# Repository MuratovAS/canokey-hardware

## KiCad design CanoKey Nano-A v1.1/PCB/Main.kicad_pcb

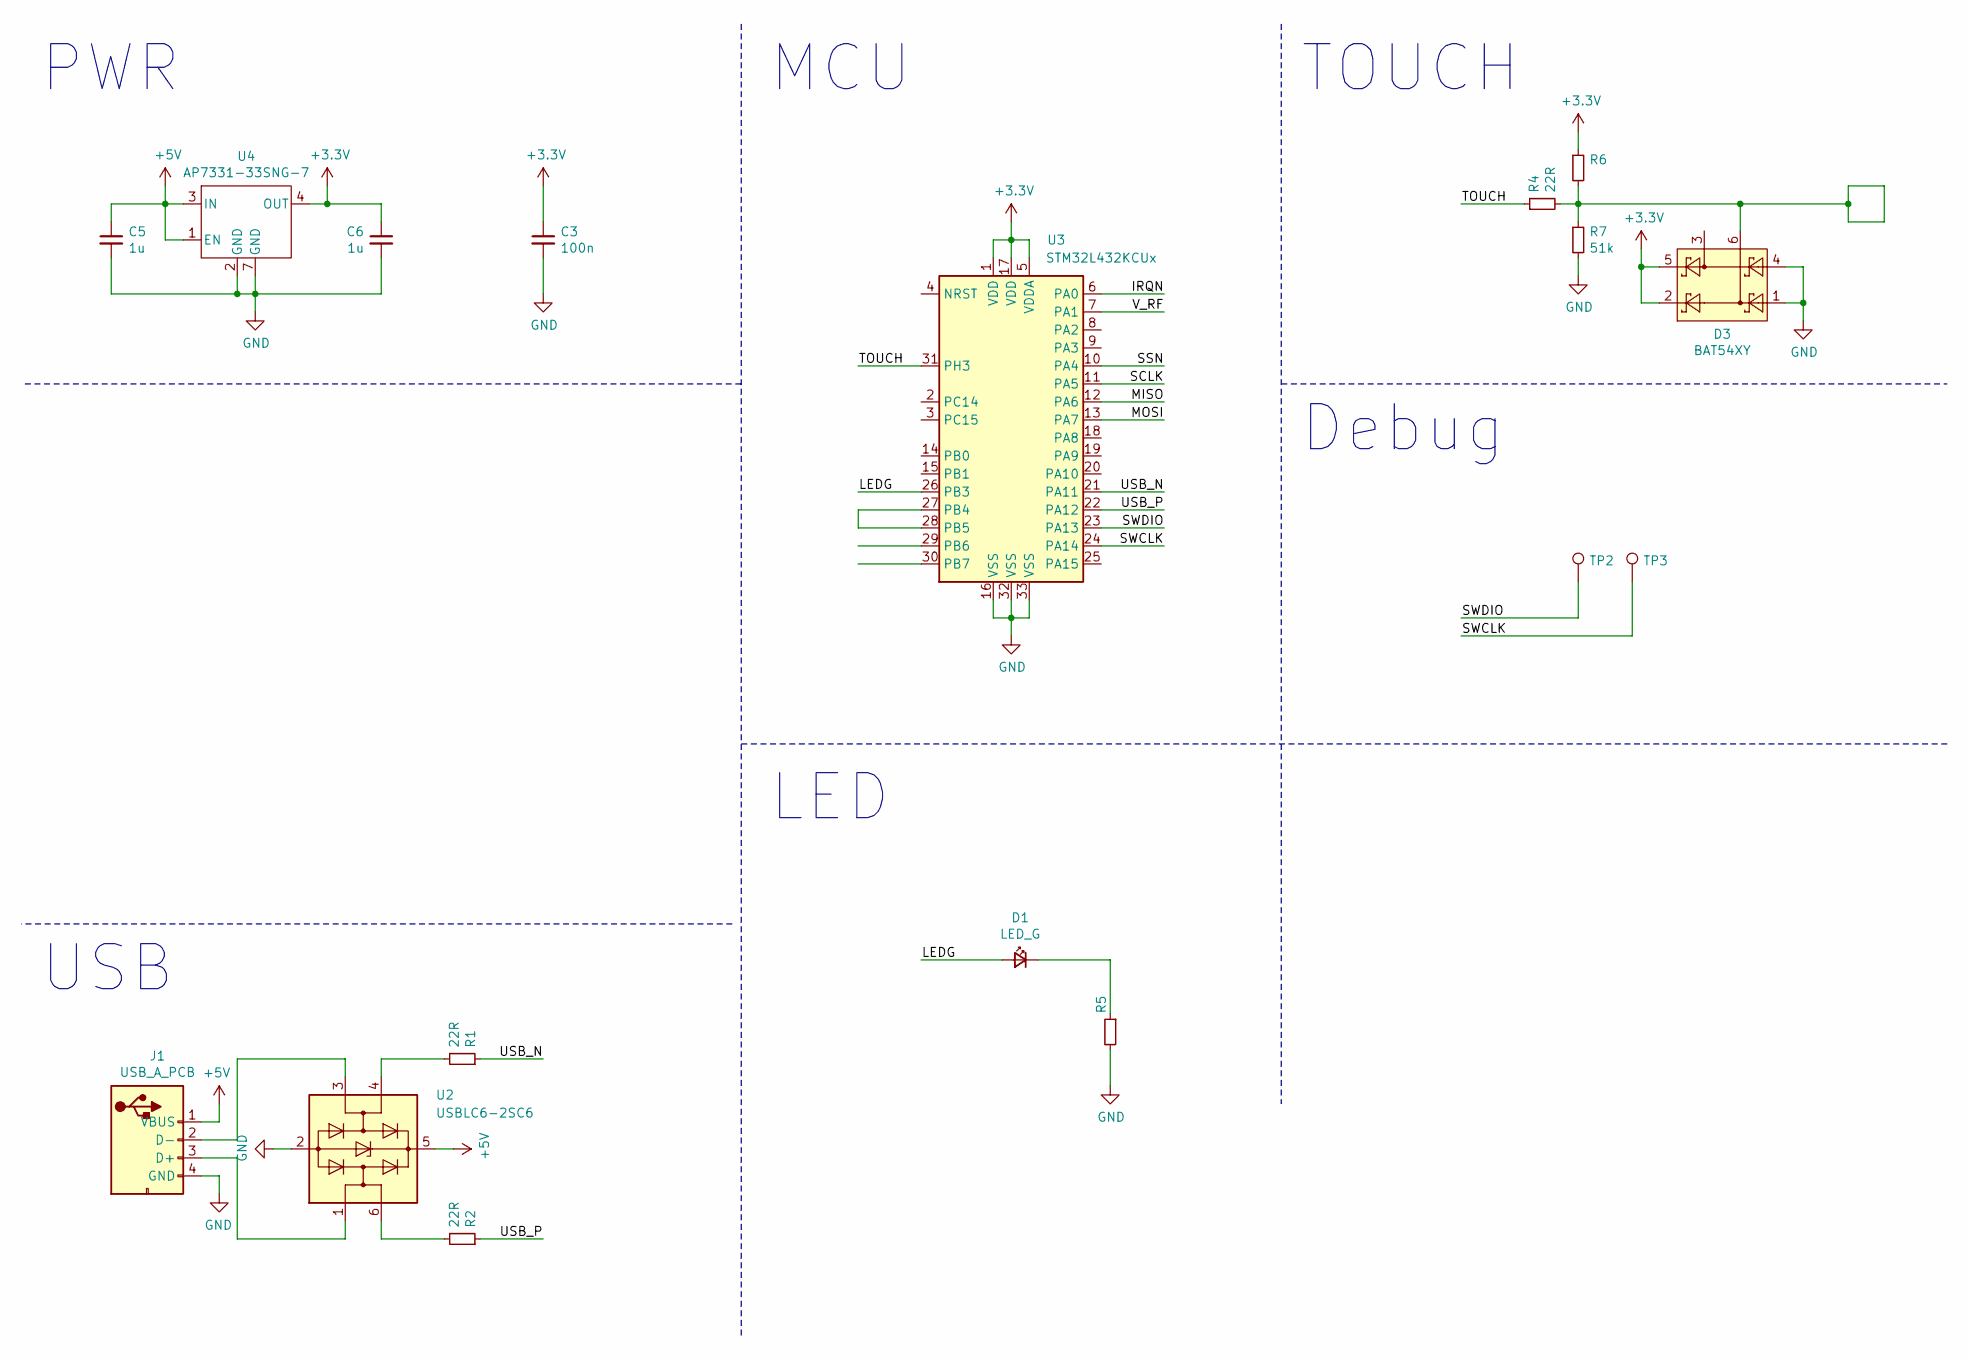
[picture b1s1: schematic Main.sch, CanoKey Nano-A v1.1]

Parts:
C3: 100n; C_0603_1608Metric; Voltage 50v; LCSC C14663
C5, C6: 1u; C_0603_1608Metric; Voltage 25v; LCSC C15849
D1: LED_G; D_0805_2012Metric
D3: BAT54XY; SOT-363_SC-70-6; LCSC C282367
J1: USB_A_PCB
R1, R2, R4: 22R; R_0603_1608Metric; Tolerance 5%; LCSC C23345
R5: 2.2k; R_0603_1608Metric; Tolerance 5%; LCSC C4190
R6: R_0603_1608Metric; Tolerance 5%
R7: 51k; R_0603_1608Metric; Tolerance 5%; LCSC C23196
TP2, TP3: TestPoint; TestPoint_Pad_D1.0mm
U2: USBLC6-2SC6; SOT-23-6; LCSC C7519
U3: STM32L432KCUx; QFN-32-1EP_5x5mm_P0.5mm_EP3.45x3.45mm; LCSC C94784
U4: AP7331-33SNG-7; UDFN-6-1EP_2x2mm_P0.65mm_EP0.9x1.65mm; LCSC C150446

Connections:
+3V3: C3.1, C6.1, D3.2, D3.5, R6.1, U3.1 (VDD), U3.5 (VDDA), U3.17 (VDD), U4.4 (OUT)
+5V: C5.1, J1.1 (VBUS), U2.5 (VBUS), U4.1 (EN), U4.3 (IN)
/IRQN: U3.6 (PA0)
/LEDG: D1.2 (A), U3.26 (PB3)
/MISO: U3.12 (PA6)
/MOSI: U3.13 (PA7)
/SCLK: U3.11 (PA5)
/SSN: U3.10 (PA4)
/SWCLK: TP3.1, U3.24 (PA14)
/SWDIO: TP2.1, U3.23 (PA13)
/TOUCH: R4.1, U3.31 (PH3)
/USB_N: R1.1, U3.21 (PA11)
/USB_P: R2.1, U3.22 (PA12)
/V_RF: U3.7 (PA1)
GND: C3.2, C5.2, C6.2, D3.1, D3.4, J1.4 (GND), R5.2, R7.2, U2.2 (GND), U3.16 (VSS), U3.32 (VSS), U3.33 (VSS), U4.2 (GND), U4.7 (GND)
unnamed: D1.1 (K), R5.1
unnamed: D3.6, R4.2, R6.2, R7.1
unnamed: J1.2 (D-), U2.3 (I/O2)
unnamed: J1.3 (D+), U2.1 (I/O1)
unnamed: R1.2, U2.4 (I/O2)
unnamed: R2.2, U2.6 (I/O1)
unnamed: U3.27 (PB4), U3.28 (PB5)

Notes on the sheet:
Debug
TOUCH
LED
USB
PWR
MCU

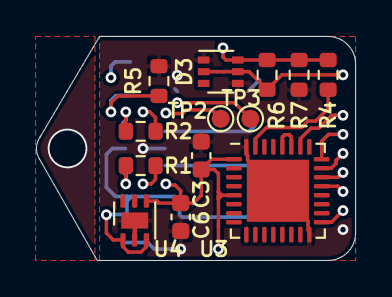
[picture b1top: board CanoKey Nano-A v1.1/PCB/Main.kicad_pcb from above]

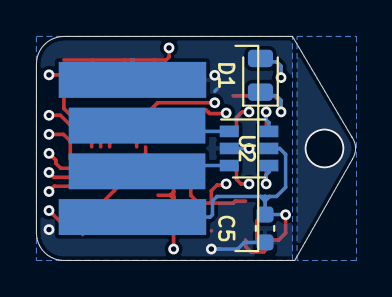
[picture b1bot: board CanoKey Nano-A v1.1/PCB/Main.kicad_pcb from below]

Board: 4 copper layers, 17.7 x 12.4 mm, 17 parts (4 on the bottom side), 16 nets.

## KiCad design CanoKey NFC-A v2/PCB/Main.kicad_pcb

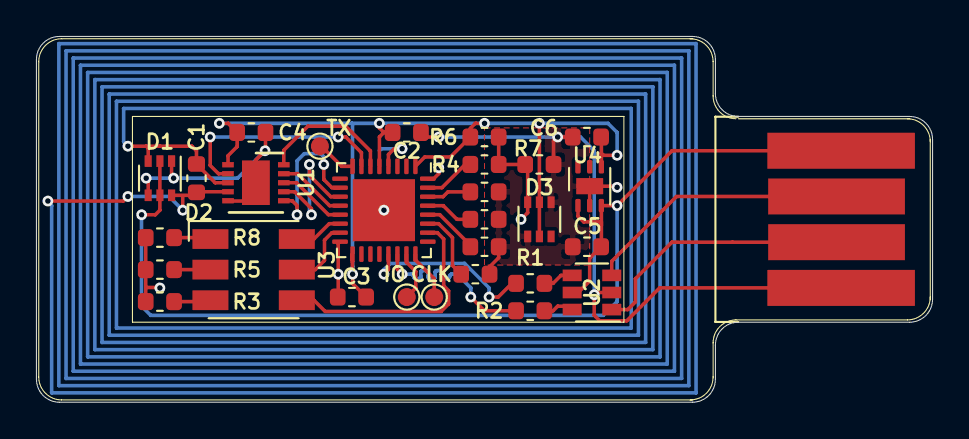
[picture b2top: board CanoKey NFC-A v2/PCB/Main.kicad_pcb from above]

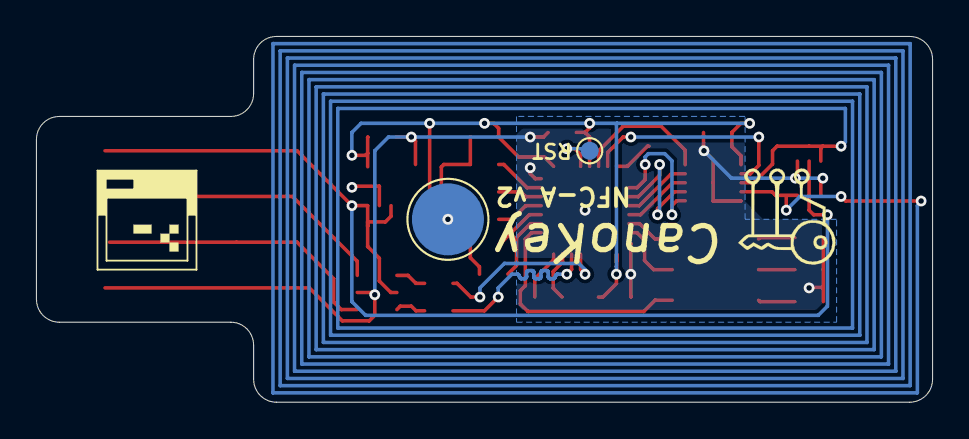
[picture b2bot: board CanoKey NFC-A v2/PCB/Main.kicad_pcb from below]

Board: 2 copper layers, 49.8 x 20.3 mm, 31 parts (2 on the bottom side), 32 nets.

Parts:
C1: C_0603_1608Metric
C2, C3, C4: 100n; C_0603_1608Metric
C5, C6: 1u; C_0603_1608Metric
D1, D3: BAT54XY; SOT-363_SC-70-6
D2: MHP5050RGBDT; LED_RGB_5050-6
J1: USB_A_PCB
R1, R2, R4: 22R; R_0603_1608Metric
R3, R5, R8: 2.2k; R_0603_1608Metric
R6, R9, R10, R11, R12: R_0603_1608Metric
R7: 51k; R_0603_1608Metric
TP1, TP2, TP3, TP5: TestPoint; TestPoint_Pad_D1.0mm
TP4: TestPoint; TestPoint_Pad_D4.0mm
U1: FM11NC08S; DFN-10-1EP_3x3mm_P0.5mm_EP1.55x2.48mm
U2: USBLC6-2SC6; SOT-23-6
U3: STM32L432KCUx; QFN-32-1EP_5x5mm_P0.5mm_EP3.45x3.45mm
U4: AP7331-33SNG-7; UDFN-6-1EP_2x2mm_P0.65mm_EP0.9x1.65mm

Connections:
+3V3: C2.1, C3.1, C4.1, C6.1, D3.2, D3.5, R6.1, U1.1, U3.1, U3.5, U3.17, U4.4
+5V: C5.1, D1.2, D1.5, J1.1, U2.5, U4.1, U4.3
/DBG_TX: TP1.1, U3.8
/IRQN: U1.10, U3.6
/L1: C1.1, C1.2, D1.3, D1.6, U1.3, U1.4
/LEDB: D2.6, U3.14
/LEDG: D2.5, U3.15
/LEDR: D2.4, U3.26
/MISO: U1.9, U3.12
/MOSI: U1.8, U3.13
/PB4: R9.2, U3.27
/PB5: R10.2, U3.28
/PB6: R11.2, U3.29
/PB7: R12.2, U3.30
/RST: TP5.1, U3.4
/SCLK: U1.7, U3.11
/SSN: U1.6, U3.10
/SWCLK: TP3.1, U3.24
/SWDIO: TP2.1, U3.23
/TOUCH: R4.1, U3.31
/USB_N: R1.1, U3.21
/USB_P: R2.1, U3.22
/V_RF: U1.2, U3.7
GND: C2.2, C3.2, C4.2, C5.2, C6.2, D1.1, D1.4, D3.1, D3.4, J1.4, R3.2, R5.2, R7.2, R8.2, R9.1, R10.1, R11.1, R12.1, U1.5, U1.11, U2.2, U3.16, U3.32, U3.33, U4.2, U4.7
unnamed: D2.1, R8.1
unnamed: D2.2, R5.1
unnamed: D2.3, R3.1
unnamed: D3.6, R4.2, R6.2, R7.1, TP4.1
unnamed: J1.2, U2.3
unnamed: J1.3, U2.1
unnamed: R1.2, U2.4
unnamed: R2.2, U2.6

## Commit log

2020-09-27 add file nano-a
2020-09-27 finalization of the nfc version
2020-09-27 add sch to nano v1.1
2020-09-27 changing the led color
2020-12-11 compact PCB
2020-12-12 fix silkscreen
